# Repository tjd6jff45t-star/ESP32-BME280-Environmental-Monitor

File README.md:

# ESP32 EnvironmentalMonitoring System

An embedded environmental monitoring system built with an ESP32 and BME280 sensor using I2C communication. The project measures temperature, humidity, and atmospheric pressure, includes sensor health monitoring with an LED status indicator, and was developed from a working breadboard prototype into a custom KiCad PCB design with completed DRC and manufacturing files.

Project Overview

The goal of this project was to design and build a complete embedded sensing system from prototype through PCB design. The system uses an ESP32 microcontroller to communicate with a BME280 environmental sensor over the I2C protocol. Firmware was written in C++ using PlatformIO to collect temperature, humidity, and pressure data, display the measurements through the Serial Monitor, and detect sensor communication failures.

After verifying the circuit on a breadboard, the design was recreated in KiCad. A custom PCB layout was developed for the ESP32 development board, BME280 breakout module, and LED status circuit. The PCB was routed, checked using KiCad's Design Rules Checker, and exported as Gerber and drill files for manufacturing.

## Technical Highlights

- Developed embedded firmware in C++ using PlatformIO and the Arduino framework.
- Communicated with a BME280 environmental sensor over I2C using ESP32 GPIO 21 for SDA and GPIO 22 for SCL.
- Verified the sensor address using an I2C scanner and confirmed communication at `0x76`.
- Measured temperature, humidity, and atmospheric pressure and displayed live values through the Serial Monitor.
- Replaced blocking `delay()` timing with `millis()`-based timing for smoother, non-blocking operation.
- Added sensor health checks to detect invalid readings and communication failures.
- Implemented an external LED status indicator for sensor operation and fault conditions.
- Designed the system schematic and PCB layout in KiCad.
- Completed PCB routing, ground copper fill, board outline, and Design Rules Check with no remaining errors.
- Generated Gerber and drill files for PCB manufacturing.

## Hardware and Tools Used

### Hardware
- ESP32 development board
- BME280 temperature, humidity, and pressure sensor
- Breadboard
- 220 Ω resistor
- LED
- Jumper wires
- USB-C cable

### Software
- Visual Studio Code
- PlatformIO
- Arduino framework
- C++
- KiCad
- GitHub

### Interfaces and Techniques
- I2C communication
- GPIO control
- PWM
- Serial debugging
- Non-blocking timing with `millis()`
- Sensor fault detection
- PCB schematic capture and layout
- Design Rules Check (DRC)
- Gerber and drill file generation

## System Operation

1. The ESP32 initializes the BME280 sensor over the I2C bus.
2. The firmware checks for the sensor at address `0x76`.
3. Once communication is established, the ESP32 reads:
   - Temperature
   - Relative humidity
   - Atmospheric pressure
4. Sensor data is printed to the Serial Monitor at regular intervals.
5. The firmware uses `millis()` instead of long blocking delays so the microcontroller can continue performing other tasks.
6. If a sensor reading is invalid or communication fails, the firmware reports an error.
7. An external LED provides a visual status indication for normal sensor operation and fault conditions.

## Prototype and Test Results

The system was first verified as a breadboard prototype before moving into PCB design.

Note: Breadboard prototype showing the ESP32 development board connected to the BME280 environmental sensor over I2C.

## Schematic and PCB Design

Note: Final KiCad schematic representing the ESP32 development board, BME280 module, and LED status circuit.

Note: Final PCB layout showing component placement, routed traces, ground copper fill, and completed board outline.

Note: KiCad 3D view of the completed PCB design used to verify component placement and board layout before manufacturing export.

## Manufacturing Outputs

The PCB design was checked using KiCad's Design Rules Checker with no remaining errors. Gerber and drill files were then generated for PCB manufacturing.

Generated fabrication files include:

- Front and back copper layers
- Front and back solder mask layers
- Front and back silkscreen layers
- Board outline (`Edge.Cuts`)
- Plated through-hole drill file
- Non-plated through-hole drill file

### I2C Communication Test
An I2C scanner was used to confirm communication between the ESP32 and the BME280. The sensor was successfully detected at address: 0x76

Note: I2C scanner output confirming successful communication with the BME280 at address 0x76.

### Environmental Sensor Readings
The ESP32 successfully collected and displayed live:

- Temperature
- Relative humidity
- Atmospheric pressure

The readings were displayed through the Serial Monitor and updated at regular intervals.

### Sensor Health Monitoring
The firmware included checks for invalid sensor readings and startup communication failures. A disconnected sensor produced an error message, while normal operation reported:

Sensor Status: OK

### LED Status Indicator
An external LED connected to GPIO 2 was used as a hardware status indicator. The LED remained active during normal sensor operation and was used to indicate fault conditions during testing.

### Challenges & What I Learned
One of the major difficulties faced in this project was moving from the functional breadboard setup to designing a PCB that faithfully represents the development boards and modules used. I started with bare chip symbols in KiCad and then updated the design to include connector-based symbols for the ESP32 development board and the BME280 breakout module. Further, I have learned how to debug serial communication, identify the I2C address of the BME280, handle cases where sensor readings fail, and improve the firmware code to replace delay() calls with calls to millis() for timing. In the PCB part of the project, I got hands-on experience in placing footprints, placing components, routing, using ground plane, defining board outline, performing DRC, and generating manufacturing files.

## Project Videos

### LED Control and PWM Test
Short demonstration of GPIO control, LED blinking, and PWM brightness control.

[Watch Video](https://youtu.be/5xzfCAMmV3Y?si=MW0iVssP8jog2qvU)

### BME280 Sensor Operation
Demonstration of the ESP32 reading temperature, humidity, and pressure from the BME280 over I2C.

[Watch Video](https://youtu.be/nWZxm4SdqU8?si=XMHZjkytFm5WDLaI)

### Sensor Fault Detection
Demonstration of the firmware detecting a disconnected BME280 sensor and reporting the fault condition.

[Watch Video](https://youtu.be/SMHI9AHuyio?si=rTMh6QFZ928x4NxT)

## Repository Contents

- `Hardware_Photos` — photos of the ESP32, BME280, breadboard prototype, and LED circuit
- `Firmware` — PlatformIO C++ firmware and project configuration
- `Schematic` — KiCad schematic files and schematic screenshots
- `PCB` — KiCad PCB files, 2D layout, and 3D board views
- `Test_Results` — I2C scan results, live sensor readings, and status verification
- `Manufacturing_Files` — Gerber and drill files generated for PCB fabrication

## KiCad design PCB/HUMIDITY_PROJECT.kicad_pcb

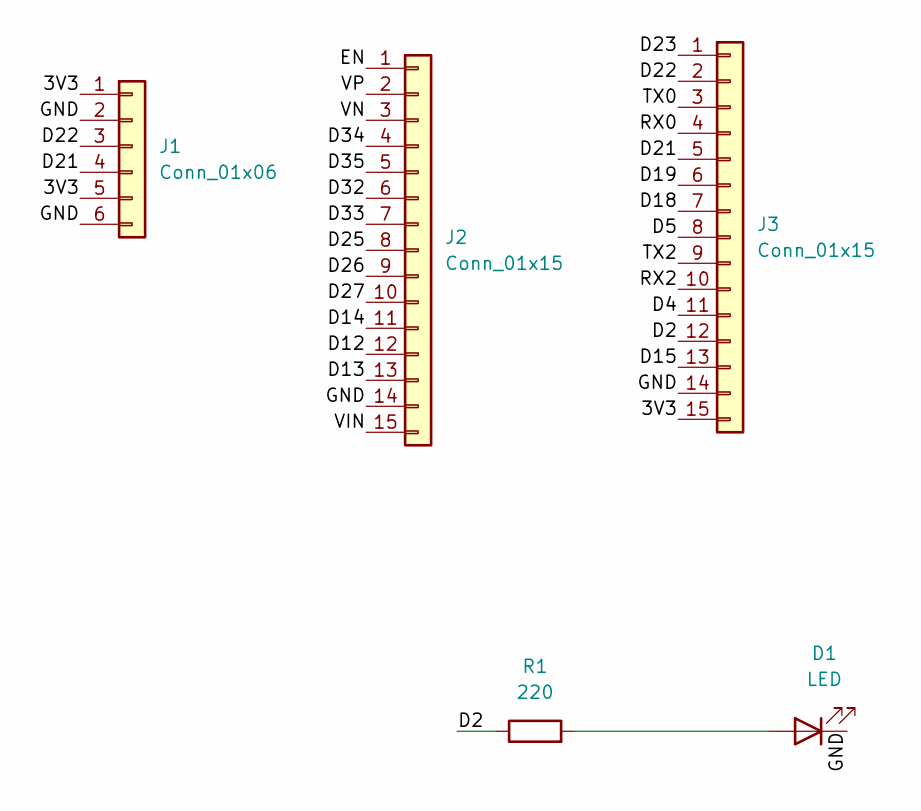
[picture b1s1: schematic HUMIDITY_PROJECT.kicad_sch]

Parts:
D1: LED; LED_D5.0mm
J1: Conn_01x06; PinHeader_1x06_P2.54mm_Vertical
J2, J3: Conn_01x15; PinHeader_1x15_P2.54mm_Vertical
R1: 220; R_Axial_DIN0207_L6.3mm_D2.5mm_P7.62mm_Horizontal

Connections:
/3V3: J1.1, J1.5, J3.15
/D2: J3.12, R1.1
/D4: J3.11
/D5: J3.8
/D12: J2.12
/D13: J2.13
/D14: J2.11
/D15: J3.13
/D18: J3.7
/D19: J3.6
/D21: J1.4, J3.5
/D22: J1.3, J3.2
/D23: J3.1
/D25: J2.8
/D26: J2.9
/D27: J2.10
/D32: J2.6
/D33: J2.7
/D34: J2.4
/D35: J2.5
/EN: J2.1
/GND: D1.1 (K), J1.2, J1.6, J2.14, J3.14
/RX0: J3.4
/RX2: J3.10
/TX0: J3.3
/TX2: J3.9
/VIN: J2.15
/VN: J2.3
/VP: J2.2
unnamed: D1.2 (A), R1.2

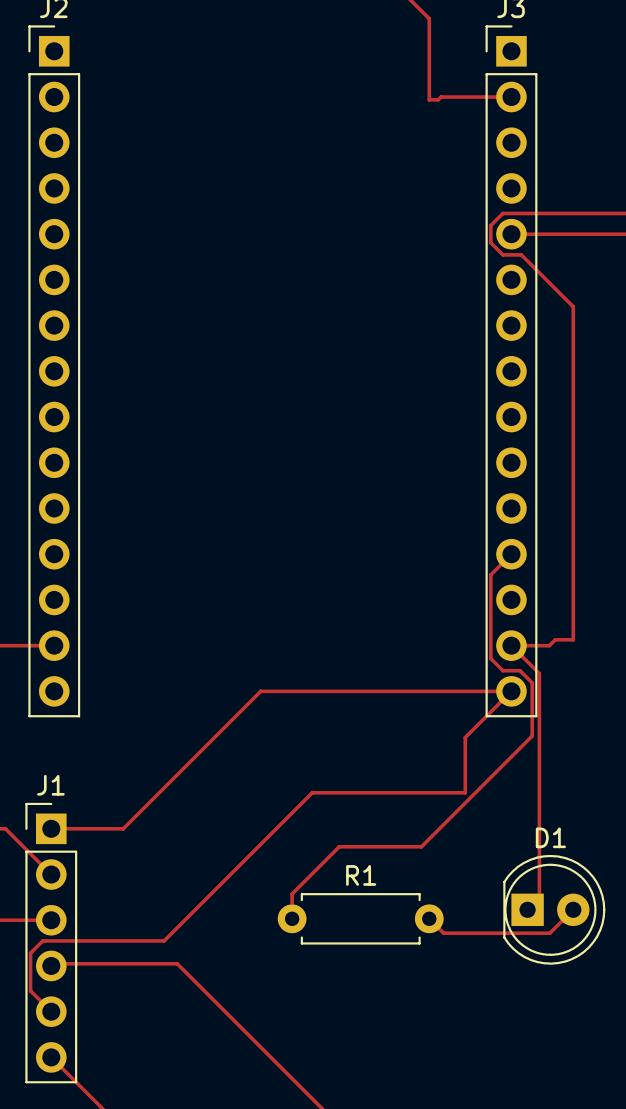
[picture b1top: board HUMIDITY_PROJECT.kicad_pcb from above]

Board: 2 copper layers, 5 parts (0 on the bottom side), 6 nets.
